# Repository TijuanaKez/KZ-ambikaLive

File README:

Ambika Live! (we'll call it that for now)

This project is a series of modifications (improvements) over the top of the YAM fork of the original firmware for Ambika.

Changes:

ENV/LFO/MOD slot cycling with page buttons:

	- Repeatedly pressing buttons for ENV/LFO and MOD pages now cycles through slots.
	- Makes for muscle memory access to what you’re after quickly. e.g (double click for LFO2)
	- Good for 2 handed operation.

Turbo patch name editing!

	- Can now press A,a or 1 to jump to those characters, insert space, or move cursor with buttons.
	- Super quick 2 handed name editing!
	- ( A | a | 1 | _ | <- | -> save | exit)

'Drum' modulation destinations.

	- Same as Osc1 and Osc2 destinations, but with +/-32 semitones range for wider pitch envelopes.
	- The standard coarse pitch mod destinations don't have enough range for good drum sounds, and the envelopes curves arent steep enough.
	- But, the standard envelopes can be 'squared' by using the modifiers for a steeper curve. Routing one of these 'squared' envelopes to 'drum' destination with an amount of 32, Ambika can achieve much better drum sounds or 808 like sounds.
	- e.g Modul.  1|srce mod1|dest drm1|amnt   32
	-     Modif.  1|in1  env1|in2  env1|oper prod  (squaring the Env1 envelope)

Solo polyphony mode:

	-Same as mono but only uses a single voice. Great if you designed a patch for a single voice (legato/glide) but want to load it onto a part that has multiple voices assigned and don’t want the unison/stacked sound.

Arp Latch Mode:

	-Acts like the arp latch on Microkorg. Pressing a key once triggers note on, a second time for note off.

Chord Sequencer mode:

	-In Chord Seq mode, the sequencer will pass each block of 4 consecutive notes on to the arp as a chord.
	-The 'lenp' parameter defines how many steps between chord changes.
	-The note sequence length is locked to 16 steps (4 chords) for now.
	-Use rests to reduce the number of notes in each chord.

Sequencer Tweaks:

	-Rests are now displayed similar to a tracker where '---' is displayed when there is no note assigned.
	-Makes for more visual drum sequences.

Performance Page Tweaks

	-When in the main performance page, the first 4 buttons now act as part mutes. Cool for jamming with the chord sequencer!
	-Button 5 resyncs the clocks. This is a bit of a workaround for the moment until I can get them to stay locked without having to resync (any ideas?)

Optional CC Maps (pref page 2)

	-Can choose between Ambika standard, Shruthi XT, and Novation Launchkey CC assignments (more to come).
	-Ideally these would be loadable from SDcard, but the only way I can think to fit them would be to use the boot loader to overwrite CC maps in progmem which is beyond my skills :frowning:

Unfortunately these mods will not be fully compatible with saved patches, though updating them would not be hard. It would mainly be checking the polyphony mode is correct, and resaving.

Work in progress…

Launchkey integration!

USB host for Launchkey via Arduino micro+micro USB Host via port 7 for connecting Launchkey directly to the Ambika.
Buss power the Arduino micro+Launchkey (might need regulator upgrade on ambika???)
Launchkey Sequencer mode: RGB pads will show sequence ‘playhead’ with one color, and knobs will edit either note, seq1 or seq2 depending on mode. Idle pads will show other colors whose intensity will represent the current sequencer values.
(‘Launchkey Seq’ mode is already in prefs page 2, but only shows the playhead now)

Source Code: Macros for enabling/disabling various functions to free up space temporarily to mess around.

The YAM fork of the original firmware can be found here (https://github.com/bjoeri/ambika).
As this is forked on top of YAM, all the YAM changes also apply.

Notes on building the source:

	- For the voicecard build to succeed, avr-gcc 4.3.3 must be used. Any later versions will build, but result in a silent voice card.
	- For the controller, avr-gcc 4.3.3 build will break our file size limit (61440 bytes)
	- But 4.5.1 will successfully build the controller and save us about 2700 bytes!!!

--- YAM Notes ---

Y A M - Yet Another Mutation

This is a project for an alternative firmware for Ambika, a hybrid MIDI polysynth and voicecard host from Mutable Instruments. 

Here's a short summary of changes _compared_ to official Ambika firmware:

* PolyBlep implementations replace the original band-limited 'saw' and 'square' oscillators for higher fidelity and less memory footprint (Polyblep implementation inspired by, but less general than, Emilies prototype for STM). 

* 'square' is now a Polyblep oscillator with more proper sounding PWM, i.e. more edginess, and no loudness drop for PWM modulation parameter above 0. 

* 'saw' is now a Polyblep oscillator (without any high pass pre-filtering and the modulation is different). The parameter for saw now add mix of a 2nd saw edge, resulting in a saw with sub oscillator (actually super oscillator) sound. 

* 'triangle' is no longer band-limited (to reduce memory footprint) and is folded (instead of clipped) upon modulation. 

* Added a quad PWM oscillator ('qpwm') very similar to the quad saw ('pad'). The modulation parameter simultaneously affects both detuning of the four pwm oscillators and the pulse width.

* Added an alternative FM oscillator ('fmfb') with feedback modulation. Just as for the regular FM oscillator, the modulation parameter defines the FM amount, but for modulation values above 64 increasing amount of feedback is added. At moderate levels the feedback adds 'grit'. At higher settings it adds digital distortion (deliberately left in).

* Added a 'csaw' Polyblep oscillator rather similar to the CS-80 inspired saw oscillator for Braids. Without modulation it's a plain saw (identical to 'saw'). Modulation adds a 'notch' discontinuity before the ramp.

* Ported phase57 mods for velocity and keyboard tracking to filter page and CC & NRPN assignments (104 and 105 respectively). Also, the active editing parameter is displayed in all uppercase characters. (http://blog.phase57.com/index.php/ambika/code for more details.) 

NOTES ON PATCH (PROGRAM) COMPATIBILITY with official Ambika firmware: 
Due to qualitative differences of the 'saw' and 'square' oscillators etc, levels may have to be adjusted somewhat to mimic original patches. If you really miss the original saw oscillator from the official firmware, this one is still available as 'oldsaw' (it's high-pass sampled and have a different character). In order to maximize patch (actually program) backwards compatibility, the added oscillators are put at the end of the oscillator selection (even though this means fmfb is not next to fm etc).

This repository was originally a copy of the Mutable Instruments GitHub Ambika repository at https://github.com/pichenettes/ambika
 
Original developer: Emilie Gillet (olivier@mutable-instruments.net)

The firmware is released under a GPL3.0 license. It includes a variant of the formant synthesis algorithm used in Peter Knight's Cantarino speech synthesizer.

The PCB layouts and schematics, documentation, analyses, simulations and 3D models are released under a Creative Commons cc-by-sa 3.0 license.

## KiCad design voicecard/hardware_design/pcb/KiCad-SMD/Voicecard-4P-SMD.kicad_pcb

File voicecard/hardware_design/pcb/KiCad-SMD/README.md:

# Voicecard-4P-SMD — Stage A (packages only)

Stage A of `docs/VOICECARD_SMD_PLAN.md`: the same 4P circuit in SMD packages,
for JLCPCB assembly. Same nets, same values, same firmware.

Provenance: copied from `../KiCad/` (the Eagle→KiCad 10 import baseline) at
commit `7cec6fe`. Only the project files were renamed; the imported symbol and
footprint libraries keep their `Voicecard-4P-v01-*` names, so every `lib_id`
in the schematic and board is unchanged. `../KiCad/` stays untouched as the
reference for the original through-hole board.

State: schematic footprints and LCSC fields assigned, ERC clean. **No board
work done** —
`Voicecard-4P-SMD.kicad_pcb` is still the original through-hole layout.

## Pin renumbering (symbol pads, not nets)

Eight Eagle symbols numbered their pins for the through-hole footprint. The
standard-library SMD footprints number pads differently, so the pin *numbers*
in the symbols were changed. Schematic wires attach to pin positions, not pin
numbers, so this changes which pad a pin lands on and nothing else; the
exported netlist is identical to the baseline's, net for net.

| Symbol | Refs | Change |
|---|---|---|
| `C-US` | C1 C27 | `+`/`-` → `1`/`2` |
| `CPOL-USE2.5-6` | C14 C25 C33 | `+`/`-` → `1`/`2` (KiCad pad 1 is +) |
| `1N47XXDO35` | D1 D2 D3 | `C`/`A` → `1`/`2` (SOD-123 pad 1 is the cathode) |
| `LED3MM` | LED1 LED2 | `K`/`A` → `1`/`2` (LED_0805 pad 1 is the cathode) |
| `2N3906-` | Q1 Q2 | TO-92 C,B,E = 1,2,3 → SOT-23 B=1, E=2, C=3 |
| `C-2.5-5/4` | C7 C13 C19 C23 | pin 3 → pad `2`; the Eagle symbol carried two alternate pads for one terminal, and the schematic wires both |
| `CRYSTALHC49U-V` | Q3 | pin 2 → pad `3`; the 3225 has the crystal on pads 1 and 3 |
| `MEGA8-P` | IC7 | DIP-28 → TQFP-32 numbering throughout |

Added pins, all of them pads the DIP package did not have:

- IC7 VCC and GND use KiCad 10 stacked numbers `[4,6]` and `[3,5]`, so the
  TQFP's second VCC and GND pads join +5V and GND. Both must be connected;
  the datasheet requires it.
- IC7 ADC6 (19) and ADC7 (22): TQFP-only ADC inputs, left unconnected.
- Q3 pads 2 and 4: the 3225's case pads, grounded (Carey, 2026-09-16) as
  convention for the package. They are one pin with the stacked number
  `[2,4]`, wired to the C31/C32 ground rail.

## Footprints and parts

JLC-assembled parts carry an `LCSC` field. Part numbers, stock and
basic/extended status were read from JLC's parts API on 2026-09-16; verify
again at order time.

| Refs | Value | Footprint | LCSC | Part | JLC |
|---|---|---|---|---|---|
| R1–R27, R29–R34 | 220/470/2.2k/10k/22k/33k | `Resistor_SMD:R_0603_1608Metric` | C22962 / C23179 / C4190 / C25804 / C31850 / C4216 | UNI-ROYAL 0603WAF, 1 % | basic |
| 16× 100n | 100n | `Capacitor_SMD:C_0603_1608Metric` | C14663 | CC0603KRX7R9BB104, 50 V X7R | basic |
| C31 C32 | 20p | `C_0603_1608Metric` | C1648 | CL10C200JB8NNNC, C0G | basic |
| C4 | 100p | `C_0603_1608Metric` | C14858 | CL10C101JB8NNNC, C0G | basic |
| C26 | 220n | `C_0603_1608Metric` | C21120 | CL10B224KA8NNNC, 25 V X7R | basic |
| C9 C10 C21 C22 | 560p | `C_0603_1608Metric` | C107054 | CC0603JRNPO9BN561, 50 V NP0 | extended |
| C7 C13 C19 C23 | 220p | `C_0603_1608Metric` | C106210 | CC0603JRNPO9BN221, 50 V NP0 | extended |
| C1 C27 | 4.7u | `Capacitor_SMD:C_1206_3216Metric` | C29823 | 1206B475K500NT, 50 V X7R | basic |
| C14 C25 C33 | 100u | `Capacitor_SMD:CP_Elec_6.3x7.7` | C72477 | RVT1E101M0607, 25 V, 6.3 × 7.7 mm | extended |
| D1 D2 | 3.6V | `Diode_SMD:D_SOD-123` | C173412 | BZT52C3V6 | extended |
| D3 | 4.7V | `Diode_SMD:D_SOD-123` | C173408 | BZT52C4V7 | extended |
| IC1 | TL074P | `Package_SO:SOIC-14_3.9x8.7mm_P1.27mm` | C12594 | TL074CDR | extended |
| IC2 | LM13700N | `Package_SO:SOIC-16_3.9x9.9mm_P1.27mm` | C174050 | LM13700MX/NOPB | extended |
| IC3 IC5 | TL072P | `Package_SO:SOIC-8_3.9x4.9mm_P1.27mm` | C6961 | TL072CDT | basic |
| IC4 | V2164D | `Package_SO:SOIC-16_3.9x9.9mm_P1.27mm` | — | SSI2164, hand-soldered | not ordered from JLC |
| IC6 | MCP4822 | `Package_SO:SOIC-8_3.9x4.9mm_P1.27mm` | C16040 | MCP4822-E/SN | extended |
| IC7 | ATMega328p | `Package_QFP:TQFP-32_7x7mm_P0.8mm` | C14877 | ATMEGA328P-AU | extended |
| Q1 Q2 | 2N3906 | `Package_TO_SOT_SMD:SOT-23` | C53444 | MMBT3906LT1G | extended |
| Q3 | 20MHz | `Crystal:Crystal_SMD_3225-4Pin_3.2x2.5mm` | C255914 | X1E0000210624, **CL 12 pF** | extended |
| LED1 LED2 | LED3MM | `LED_SMD:LED_0805_2012Metric` | C84256 | NCD0805R1, red | basic |

Value fields still read as the original parts (`TL074P`, `2N3906`,
`LED3MM`, …) because Stage A does not change values; the `LCSC` field carries
the part that is actually fitted.

Crystal load capacitance: C31/C32 stay at 20 p — two 20 p in series is 10 pF,
plus a few pF of stray, so 12–14 pF. Hence the 12 pF-load crystal. A 20 pF-load
part such as C9004 would mean changing those values, which Stage A does not do.

### Kept through-hole

JP1–JP4, ISP0 and R28 keep their imported Eagle footprints. JP1–JP4 are
mechanically locked to the motherboard, and the imported footprints are
anchored the way the baseline board places them; the standard-library pin
headers are anchored on pad 1 and would shift the connectors. Per the plan
these six parts (four headers, the trimmer, the SSI2164) are hand-soldered on
arrival, so they carry no LCSC field.

R28's imported footprint is the triangular Bourns 3296P pad pattern, matching
KiCad's `Potentiometer_Bourns_3296P_Horizontal`, not the 3296W named in the
plan. Kept through-hole for Stage A (Carey, 2026-09-16): it is the pattern the
original used, and the card is already being finished by hand. An SMD 3224W
is a question for the STM32 board.

## ERC

`kicad-cli sch erc` reports **0 errors and 1 warning**: IC2 has unplaced units
A and B, the LM13700's two Darlington buffers, unused in the 4P (pins 7–10).
That warning is inherent to using half of an LM13700 and is left alone; it is
also what Update PCB from Schematic reports about pads 7–10.

The Eagle import arrived with 20 ERC errors, all of them missing annotation
rather than circuit faults, and all cleared here (Carey, 2026-09-16) so that a
real error is visible later. No net and no value changed:

- 13 no-connect flags on pins that are unused by design: IC7 AREF, PC0–PC3,
  PD0, PD3, PD7, PB0, PB1; IC2 pins 2 and 15 (LM13700 diode-bias inputs);
  IC4 pin 1 (2164 MODE). ADC6/ADC7 on the TQFP need no flag — those pins are
  declared as no-connect in the symbol.
- 4 PWR_FLAGs, on +5V, VCC, VEE and GND, telling ERC where power enters the
  card. They sit on the existing supply symbols' pins; their value text is
  hidden so it does not cover JP2's pin numbers. PWR_FLAG lives in
  `Voicecard-4P-SMD-extras.kicad_sym`, a project library, so the schematic
  does not depend on KiCad's global symbol libraries. Flags carry no
  footprint and stay out of the BOM.

These flags exist only in KiCad-SMD; `../KiCad/` keeps its original ERC state.

## Reproducing the checks

```sh
KC=/Applications/KiCad/KiCad.app/Contents/MacOS/kicad-cli
$KC sch erc --severity-all -o erc.rpt Voicecard-4P-SMD.kicad_sch
$KC sch export netlist --format kicadsexpr -o smd.net Voicecard-4P-SMD.kicad_sch
$KC sch export bom --fields "Reference,Value,Footprint,LCSC,\${QUANTITY}" \
    --group-by "Value,Footprint,LCSC" -o bom.csv Voicecard-4P-SMD.kicad_sch
```

## Board preparation (done, nothing placed)

The board was updated from the schematic with footprints replaced in place:
each footprint sits at its predecessor's position, orientation and layer, and
keeps its schematic path. kicad-cli has no update-from-schematic command and
pcbnew does not wrap `BOARD_NETLIST_UPDATER`, so `board_prep.py` does it
explicitly through pcbnew and the result is checked against the schematic
netlist rather than trusted:

| Check | Result |
|---|---|
| Footprints | 92 (81 replaced, 5 board-only: U$1 U$2 U$4 U$5 U$6, 6 kept THT) |
| Pad nets vs schematic netlist | 277 of 277, no mismatch, nothing extra |
| Nets | same set as the schematic, none added or lost |
| Library ids | all library-qualified (`Resistor_SMD:R_0603...`) |
| Tracks / vias / zones | 445 segments, 20 vias and 1 zone deleted; 0 remain |
| Locked | Edge.Cuts (8 segments), U$1 U$2 U$4 U$5, JP1–JP4, ISP0 |
| Outline | 118.8 × 60.38 mm, unchanged |

IC2 pads 7–10 carry no net: the LM13700 buffer half the 4P does not use.

### Design rules and net classes

JLCPCB 2-layer standard, set in the `.kicad_pro`:

| Rule | Was | Now |
|---|---|---|
| Minimum track width | 0.2 | **0.127 mm** |
| Minimum clearance | 0.2032 | **0.127 mm** |
| Minimum via drill | 0.3 | 0.3 mm |
| Minimum via diameter | 0.5 | **0.6 mm** |

| Net class | Track | Via | Nets |
|---|---|---|---|
| Default | 0.2 mm | 0.6 / 0.3 mm | everything else |
| Power | 0.4 mm | 0.6 / 0.3 mm | +5V, VCC, VEE, GND |

### Light placement pass

Olivier's arrangement is kept: nothing was compacted or regrouped, and the
rows of passives stay where they were. Only these moved (`place.py`):

**Decoupling.** Every 100n sat 5.97–13.99 mm from the supply pins it serves,
because the SOIC and TQFP bodies are so much smaller than the DIPs they
replaced. Each is now beside its IC's supply pad, assigned to minimise total
travel:

| Cap | Serves | Gap |
|---|---|---|
| C16 / C3 | IC1 VCC pad 4 / VEE pad 11 | 2.88 / 2.88 mm |
| C5 / C18 | IC2 VCC pad 11 / VEE pad 6 | 1.32 / 1.32 mm |
| C6 / C20 | IC3 VCC pad 8 / VEE pad 4 | 1.32 / 1.32 mm |
| C8 / C11 | IC4 VCC pad 16 / VEE pad 9 | 1.28 / 1.55 mm |
| C12 / C24 | IC5 VCC pad 8 / VEE pad 4 | 1.32 / 1.32 mm |
| C29 | IC6 VDD pad 1 | 1.58 mm |
| C30 | IC7 VCC pads 4 and 6 | 2.42 / 2.83 mm |
| C28 | IC7 AVCC pad 18 | 0.88 mm |

**Crystal loop.** Q3, C31 and C32 moved from 10–17 mm away to sit against
IC7's XTAL pins: Q3's terminals are now 1.65 mm (XTAL2, pad 8) and 3.35 mm
(XTAL1, pad 7) from the MCU, with the load caps flanking the crystal. The
3225's two terminals are diagonally opposite, so one of them is always the
far one; the two placements are within 0.05 mm of each other in total length.

**C33** moved from the bottom-right corner, where its pad crossed the board
edge, to the free band at (191.5, 113.5). It could not simply move inboard:
that corner is boxed in by the U$5 mounting hole, ISP0, R33 and JP4, and the
9.5 mm can does not fit between them.

**Q1 and Q2 are not an expo pair, so they were left alone.** Read from the
netlist: each is a separate op-amp servo current source. Q1's base is driven
by IC1D's output with R1 from its emitter back to IC1D's inverting input, and
its collector feeds I_GAIN (IC2 pin 16); Q2 is the same topology around IC1A
with R12, feeding I_RESO (IC2 pin 1). They share no node, and neither is an
exponential converter — the V/Oct exponential conversion is internal to the
SSI2164, whose four CTRL pins are driven from F_CV via IC1B, with R28 (the
trimmer silkscreened V/Oct) setting the scale through R15. Placing them
touching would buy nothing.

**Grid and orientation.** All unlocked footprints are on a 0.5 mm grid, except
C25, which has 0.06 mm of slack between JP1 and JP3 and so keeps its imported
position rather than being nudged into a locked connector. 24 0603 parts had
their orientation normalised to their own axis (-90 to 90, 180 to 0) so each
group agrees; nothing was rotated by 90 degrees, so no pad moved.

Locked parts — connectors, mounting holes, the outline — did not move.

### DRC after placement

```
** Found 88 DRC violations **
** Found 196 unconnected items **

 196  [unconnected_items]      error    <- nothing routed yet
  51  [silk_over_copper]       warning
  25  [silk_overlap]           warning
   6  [silk_edge_clearance]    warning
   4  [lib_footprint_mismatch] warning
   2  [text_height]            warning
```

`copper_edge_clearance` is **zero**, as is `courtyards_overlap`. The
silkscreen warnings rose from 57 to 82 because parts are now closer together;
that is for the silkscreen pass after routing, where plan §3 turns values off
and leaves reference designators on for JLC's assembly drawing. The 4 library
mismatches are still the Eagle-imported mounting holes.

Renders and the ratsnest drawing are written to `build/` (gitignored):
`voicecard-4p-smd-front.png`, `-back.png`, `-ratsnest.png`.

## Next (not done)

Placement, then routing. The outline, mounting holes and connectors are
locked, so placement starts from them. Plan §3 layout rules apply: analog
section together and away from the AVR clock and DAC lines, GND pour both
sides stitched, values off the silkscreen.

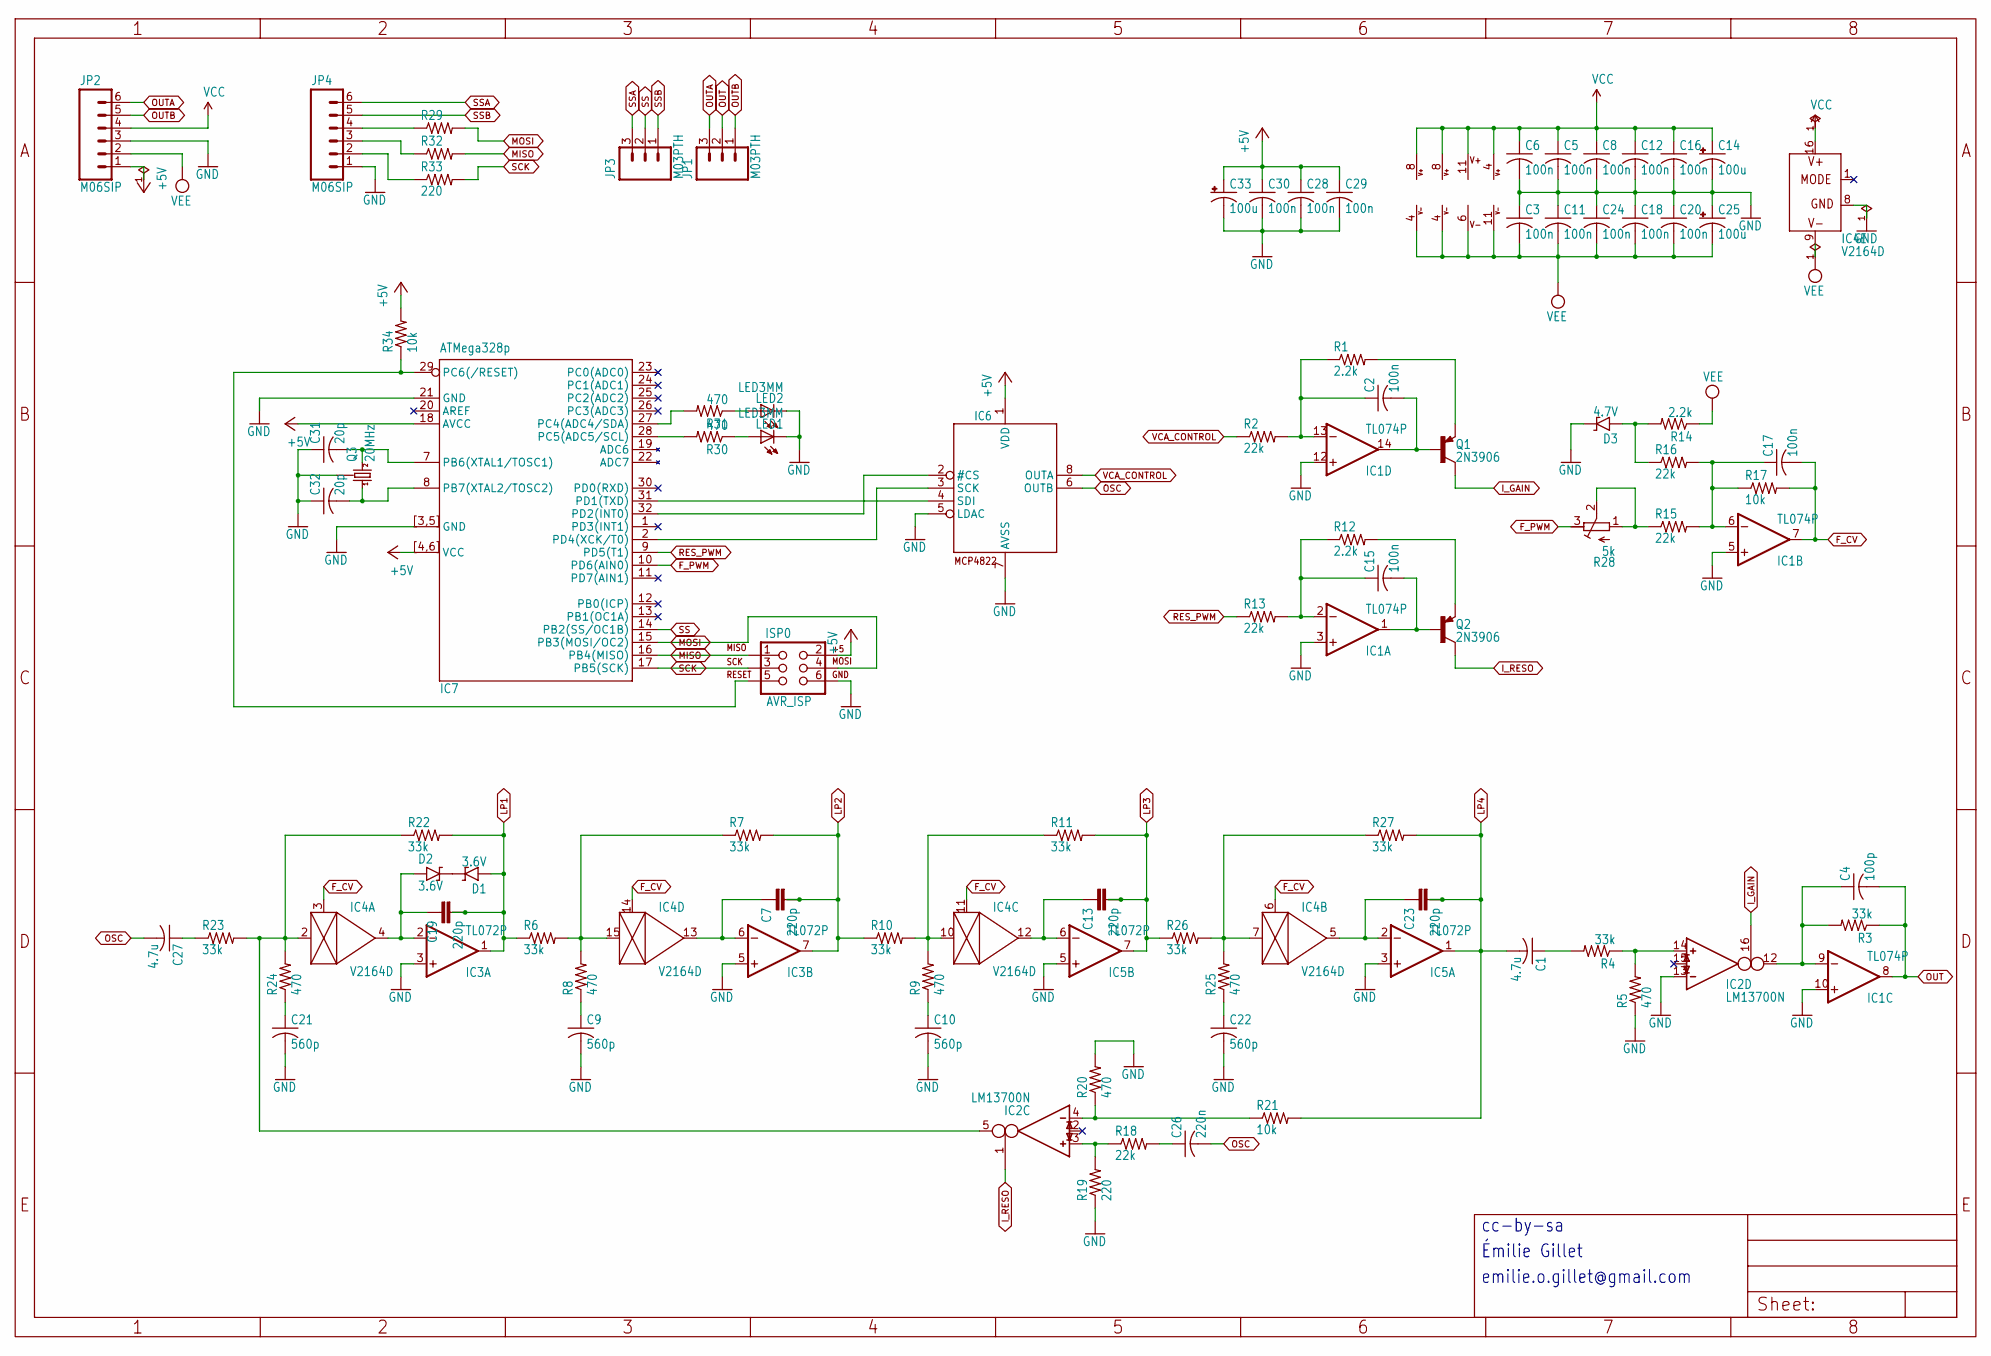
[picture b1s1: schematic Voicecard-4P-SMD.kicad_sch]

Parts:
C1, C27: 4.7u; C_1206_3216Metric; LCSC C29823
C2, C3, C5, C6, C8, C11, C12, C15, C16, C17, C18, C20, C24, C28, C29, C30: 100n; C_0603_1608Metric; LCSC C14663
C4: 100p; C_0603_1608Metric; LCSC C14858
C7, C13, C19, C23: 220p; C_0603_1608Metric; LCSC C106210
C9, C10, C21, C22: 560p; C_0603_1608Metric; LCSC C107054
C14, C25, C33: 100u; CP_Elec_6.3x7.7; LCSC C72477
C26: 220n; C_0603_1608Metric; LCSC C21120
C31, C32: 20p; C_0603_1608Metric; LCSC C1648
D1, D2: 3.6V; D_SOD-123; LCSC C173412
D3: 4.7V; D_SOD-123; LCSC C173408
IC1: TL074P; SOIC-14_3.9x8.7mm_P1.27mm; LCSC C12594
IC2: LM13700N; SOIC-16_3.9x9.9mm_P1.27mm; LCSC C174050
IC3, IC5: TL072P; SOIC-8_3.9x4.9mm_P1.27mm; LCSC C6961
IC4: V2164D; SOIC-16_3.9x9.9mm_P1.27mm
IC6: MCP4822; SOIC-8_3.9x4.9mm_P1.27mm; LCSC C16040
IC7: ATMega328p; TQFP-32_7x7mm_P0.8mm; LCSC C14877
ISP0: AVR_ISP; 2X3
JP1, JP3: M03PTH; 1X03
JP2, JP4: M06SIP; 1X06
LED1, LED2: LED3MM; LED_0805_2012Metric; LCSC C84256
Q1, Q2: 2N3906; SOT-23; LCSC C53444
Q3: 20MHz; Crystal_SMD_3225-4Pin_3.2x2.5mm; LCSC C255914
R1, R12, R14: 2.2k; R_0603_1608Metric; LCSC C4190
R2, R13, R15, R16, R18: 22k; R_0603_1608Metric; LCSC C31850
R3, R4, R6, R7, R10, R11, R22, R23, R26, R27: 33k; R_0603_1608Metric; LCSC C4216
R5, R8, R9, R20, R24, R25, R30, R31: 470; R_0603_1608Metric; LCSC C23179
R17, R21, R34: 10k; R_0603_1608Metric; LCSC C25804
R19, R29, R32, R33: 220; R_0603_1608Metric; LCSC C22962
R28: 5k; RTRIM3296P

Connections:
+5V: C28.1, C29.1, C30.1, C33.1 (+), IC6.1 (VDD), IC7.4, IC7.6, IC7.18 (AVCC), IC7.[4,6] (VCC), ISP0.2, JP2.1, R34.2
F_CV: C17.2, IC1.7 (OUT), IC4.3 (CTRL), IC4.6 (CTRL), IC4.11 (CTRL), IC4.14 (CTRL), R17.2
F_PWM: IC7.10 (PD6(AIN0)), R28.3 (A)
GND: C3.1, C5.2, C6.2, C8.2, C9.2, C10.2, C11.1, C12.2, C14.2 (-), C16.2, C18.1, C20.1, C21.2, C22.2, C24.1, C25.1 (+), C28.2, C29.2, C30.2, C31.1, C32.1, C33.2 (-), D3.1 (C), IC1.3 (+IN), IC1.5 (+IN), IC1.10 (+IN), IC1.12 (+IN), IC2.13 (IN_N), IC3.3 (+IN), IC3.5 (+IN), IC4.8 (GND), IC5.3 (+IN), IC5.5 (+IN), IC6.5 (LDAC), IC6.7 (AVSS), IC7.3, IC7.5, IC7.21 (GND), IC7.[3,5] (GND), ISP0.6, JP2.3, JP4.1, LED1.1 (C), LED2.1 (C), Q3.2, Q3.4, Q3.[2,4] (GND), R5.1, R19.1, R20.2
I_GAIN: IC2.16 (I_BIAS), Q1.3 (C)
I_RESO: IC2.1 (I_BIAS), Q2.3 (C)
LP1: C19.2, D1.2 (A), IC3.1 (OUT), R6.1, R22.2
LP2: C7.2, IC3.7 (OUT), R7.2, R10.1
LP3: C13.2, IC5.7 (OUT), R11.2, R26.1
LP4: C1.2, C23.2, IC5.1 (OUT), R21.2, R27.2
MISO: IC7.16 (PB4(MISO)), ISP0.1, R32.2
MOSI: IC7.15 (PB3(MOSI/OC2)), ISP0.4, R29.2
unnamed: C1.1, R4.2
unnamed: C9.1, R8.1
unnamed: C10.1, R9.1
unnamed: C21.1, R24.1
unnamed: C22.1, R25.1
unnamed: C26.1, R18.2
unnamed: C27.1, R23.1
unnamed: D1.1 (C), D2.1 (C)
unnamed: C19.1, D2.2 (A), IC3.2 (-IN), IC4.4 (OUT)
unnamed: D3.2 (A), R14.2, R16.1
unnamed: C15.1, IC1.2 (-IN), R12.1, R13.2
unnamed: C15.2, IC1.1 (OUT), Q2.1 (B)
unnamed: C17.1, IC1.6 (-IN), R15.2, R16.2, R17.1
unnamed: C4.1, IC1.9 (-IN), IC2.12 (OUT), R3.2
unnamed: C2.1, IC1.13 (-IN), R1.1, R2.2
unnamed: C2.2, IC1.14 (OUT), Q1.1 (B)
unnamed: IC2.4 (IN_N), R20.1, R21.1
unnamed: IC2.3 (IN_P), R18.1, R19.2
unnamed: IC2.5 (OUT), IC4.2 (IN), R22.1, R23.2, R24.2
unnamed: IC2.14 (IN_P), R4.1, R5.2
unnamed: C7.1, IC3.6 (-IN), IC4.13 (OUT)
unnamed: IC4.7 (IN), R25.2, R26.2, R27.1
unnamed: C23.1, IC4.5 (OUT), IC5.2 (-IN)
unnamed: IC4.10 (IN), R9.2, R10.2, R11.1
unnamed: C13.1, IC4.12 (OUT), IC5.6 (-IN)
unnamed: IC4.15 (IN), R6.2, R7.1, R8.2
unnamed: IC6.2 (#CS), IC7.32 (PD2(INT0))
unnamed: IC6.3 (SCK), IC7.2 (PD4(XCK/T0))
unnamed: IC6.4 (SDI), IC7.31 (PD1(TXD))
unnamed: C31.2, IC7.7 (PB6(XTAL1/TOSC1)), Q3.3 (2)
unnamed: C32.2, IC7.8 (PB7(XTAL2/TOSC2)), Q3.1
unnamed: IC7.27 (PC4(ADC4/SDA)), R31.2
unnamed: IC7.28 (PC5(ADC5/SCL)), R30.2
unnamed: IC7.29 (PC6(/RESET)), ISP0.5, R34.1
unnamed: JP4.2, R33.1
unnamed: JP4.3, R32.1
unnamed: JP4.4, R29.1
unnamed: LED1.2 (A), R30.1
unnamed: LED2.2 (A), R31.1
unnamed: Q1.2 (E), R1.2
unnamed: Q2.2 (E), R12.2
unnamed: R15.1, R28.1 (E), R28.2 (S)
OSC: C26.2, C27.2, IC6.6 (OUTB)
OUT: C4.2, IC1.8 (OUT), JP1.2, R3.1
OUTA: JP1.3, JP2.6
OUTB: JP1.1, JP2.5
RES_PWM: IC7.9 (PD5(T1)), R13.1
SCK: IC7.17 (PB5(SCK)), ISP0.3, R33.2
SS: IC7.14 (PB2(SS/OC1B)), JP3.2
SSA: JP3.3, JP4.6
SSB: JP3.1, JP4.5
VCA_CONTROL: IC6.8 (OUTA), R2.1
VCC: C5.1, C6.1, C8.1, C12.1, C14.1 (+), C16.1, IC1.4 (V+), IC2.11 (V+), IC3.8 (V+), IC4.16 (V+), IC5.8 (V+), JP2.4
VEE: C3.2, C11.2, C18.2, C20.2, C24.2, C25.2 (-), IC1.11 (V-), IC2.6 (V-), IC3.4 (V-), IC4.9 (V-), IC5.4 (V-), JP2.2, R14.1

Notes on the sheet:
Émilie Gillet
cc-by-sa
emilie.o.gillet@gmail.com

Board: 2 copper layers, 92 parts (0 on the bottom side), 66 nets, no tracks yet.

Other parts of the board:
U$1, U$2: 3,0
U$4, U$5: 3,3
U$6: V2_LOGO_SMALL
